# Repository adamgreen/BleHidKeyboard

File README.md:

# BLE HID Keyboard
A project to convert a [Perixx PERIDUO-307B USB wired keyboard](https://www.amazon.com/Perixx-PERIBOARD-407B-Mini-Keyboard-Dimension/dp/B0053O9ZNQ/) to wireless Bluetooth Low Energy (BLE). The conversion is accomplished by replacing the original PCB with the one documented here which uses a [Nordic nRF51422](https://www.nordicsemi.com/eng/Products/ANT/nRF51422) BLE capable ARM Cortex-M0 microcontroller. This repository includes the Eagle CAD PCB design files and firmware source code.

## Bill of Materials
Description | Quantity | Part Number(s)
------------|----------|---------------
[Perixx PERIDUO-307B USB wired keyboard](https://www.amazon.com/Perixx-PERIBOARD-407B-Mini-Keyboard-Dimension/dp/B0053O9ZNQ/) | 1 |
[SODIAL 3W LED Mini Pen Torch Flashlight 2xAAA](https://www.amazon.com/gp/product/B01J58ZHOG) | 1 |
[1.2kΩ Resistor - 0805](https://www.adafruit.com/product/441) | 3 | R1, R2, R3
[Microchip MCP23018 I2C I/O Expander](https://www.digikey.com/product-detail/en/microchip-technology/MCP23018-E-SS/MCP23018-E-SS-ND/1999506) | 2 | IC1, IC2
[Samtec 2x5 SMT Micro Header](https://www.digikey.com/product-detail/en/FTSH-105-01-L-DV-K/SAM8799-ND/1875039) | 1 | JP1
[Dynastream N5150M5CD - nRF51422 Module](https://www.digikey.com/products/en?keywords=N5150M5CD) | 1 | U1
[Green SMT LED](https://www.digikey.com/product-detail/en/kingbright/APTD3216LCGCK/754-2049-1-ND/7043101) | 3 | LED_CAPS, LED_CONNECT, LED_NUM LED

It also requires a 2x13 ribbon cable connector harvested from the original PCB using a [Chip Quick SMD Removal Kit](https://www.adafruit.com/product/2660).

## Firmware Build
I have only tested the build on macOS but it will probably work on other Posix operating systems too.

**Note:** Building the firmware and deploying it to the nRF51 requires the **mergehex** and **nrfjprog** tools. The archive for your OS can be downloaded from the _Downloads_ tab of the [nRF51422 product page](https://www.nordicsemi.com/eng/Products/Bluetooth-low-energy/nRF51422). You will also need a SEGGER J-Link JTAG/SWD Debugger. If your projects are of a non-commercial nature, you can use this [low cost module available from Adafruit](https://www.adafruit.com/product/3571).

* ```make sdk``` will download and install the required Nordic SDK. This should only need to be done once.
* ```make flash_softdevice``` will install the required Nordic SoftDevice on the nRF51422 microcontroller using the J-Link debugger. This will typically only need to be done once for each microcontroller.
* ```make all``` will build the keyboard firmware.
* ```make flash```will build the keyboard firmware and deploy it using the J-Link debugger.
* ```make generate_patches``` can be used to generate diffs for any files that you have modified in the [config/ subfolder](https://github.com/adamgreen/BleHidKeyboard/tree/master/firmware/config) so that you can commit and share them via git.

## Photos
**Perixx PERIDUO-307B USB Wired Keyboard**<br>
<br>

**Inside of Keyboard with Original PCB**<br>
<br>

**Inside of Keyboard with New BLE PCB**<br>
<br>

**Peeking Under Membrane at New BLE PCB**<br>
<br>

**Inside of Keyboard After Modifications**<br>
<br>

**Keyboard with 2xAAA Torchlight as Battery Pack**<br>
<br>

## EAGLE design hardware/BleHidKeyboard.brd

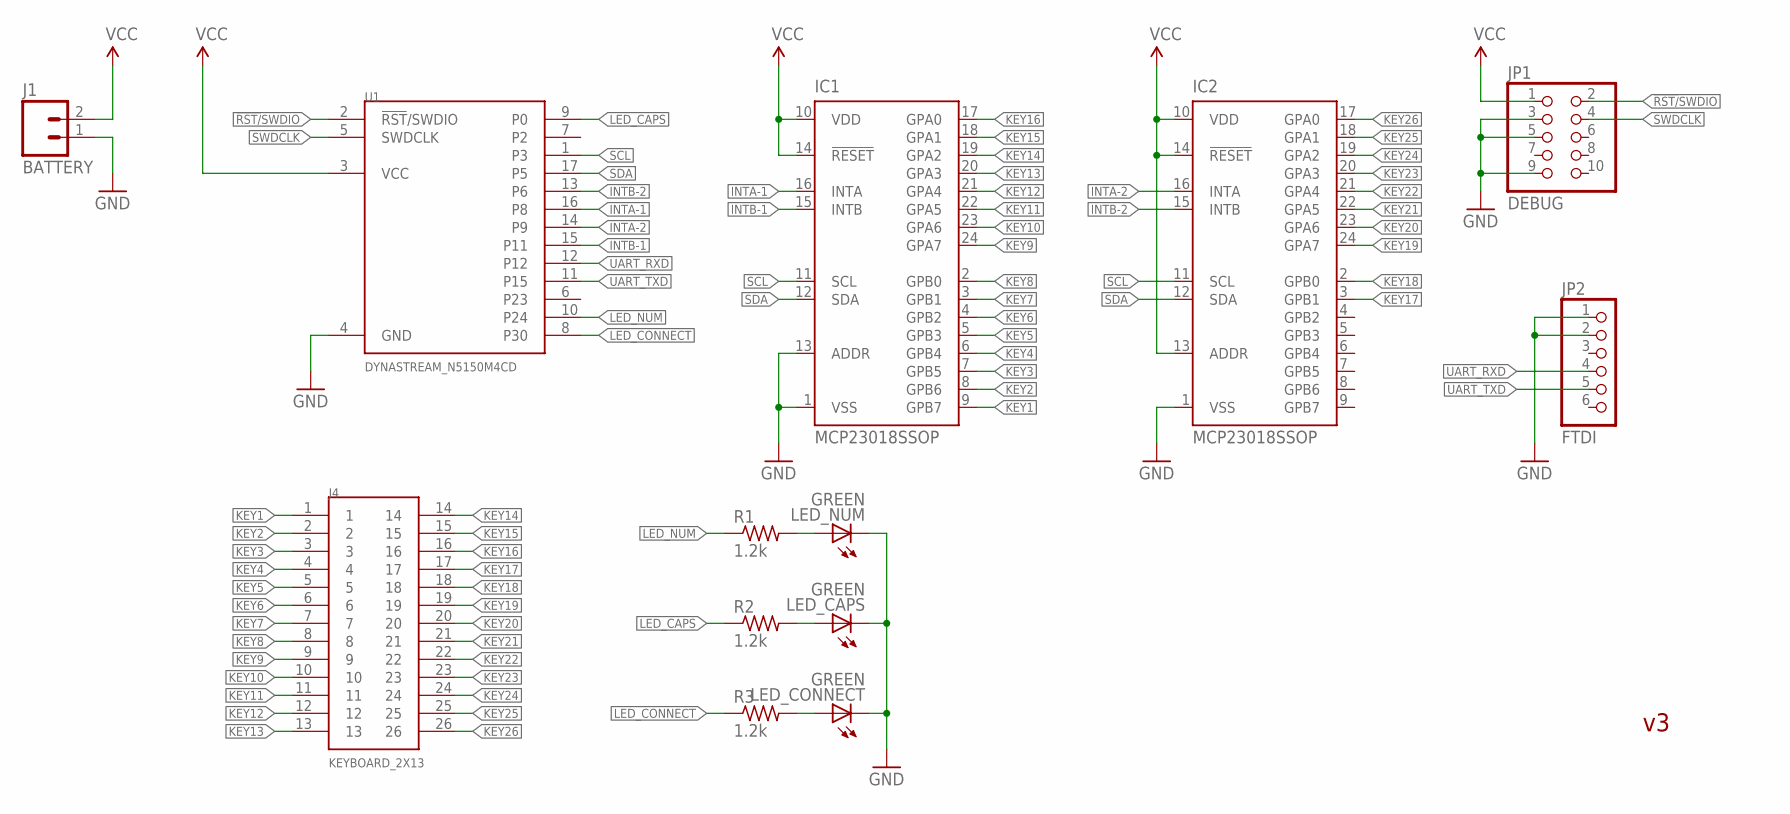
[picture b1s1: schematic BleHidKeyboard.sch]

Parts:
IC1, IC2: MCP23018SSOP; SSOP24
J1: BATTERY; 1X02_NO_SILK
J4: KEYBOARD_2X13
JP1: DEBUG; FTSH-105
JP2: FTDI; 1X06-CLEAN
LED_CAPS: GREEN; CHIPLED_1206
LED_CONNECT: GREEN; CHIPLED_1206
LED_NUM: GREEN; CHIPLED_1206
R1, R2, R3: 1.2k; R0805
U1: DYNASTREAM_N5150M4CD; N5150M4CD

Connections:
!RST/!SWDIO: JP1.2, U1.2 (!RST!/SWDIO)
GND: IC1.1 (VSS), IC1.13 (ADDR), IC2.1 (VSS), J1.1, JP1.3, JP1.5, JP1.9, JP2.1, JP2.2, LED_CAPS.C, LED_CONNECT.C, LED_NUM.C, U1.4 (GND)
INTA-1: IC1.16 (INTA), U1.16 (P8)
INTA-2: IC2.16 (INTA), U1.14 (P9)
INTB-1: IC1.15 (INTB), U1.15 (P11)
INTB-2: IC2.15 (INTB), U1.13 (P6)
KEY1: IC1.9 (GPB7), J4.1
KEY2: IC1.8 (GPB6), J4.2
KEY3: IC1.7 (GPB5), J4.3
KEY4: IC1.6 (GPB4), J4.4
KEY5: IC1.5 (GPB3), J4.5
KEY6: IC1.4 (GPB2), J4.6
KEY7: IC1.3 (GPB1), J4.7
KEY8: IC1.2 (GPB0), J4.8
KEY9: IC1.24 (GPA7), J4.9
KEY10: IC1.23 (GPA6), J4.10
KEY11: IC1.22 (GPA5), J4.11
KEY12: IC1.21 (GPA4), J4.12
KEY13: IC1.20 (GPA3), J4.13
KEY14: IC1.19 (GPA2), J4.14
KEY15: IC1.18 (GPA1), J4.15
KEY16: IC1.17 (GPA0), J4.16
KEY17: IC2.3 (GPB1), J4.17
KEY18: IC2.2 (GPB0), J4.18
KEY19: IC2.24 (GPA7), J4.19
KEY20: IC2.23 (GPA6), J4.20
KEY21: IC2.22 (GPA5), J4.21
KEY22: IC2.21 (GPA4), J4.22
KEY23: IC2.20 (GPA3), J4.23
KEY24: IC2.19 (GPA2), J4.24
KEY25: IC2.18 (GPA1), J4.25
KEY26: IC2.17 (GPA0), J4.26
LED_CAPS: R2.1, U1.9 (P0)
LED_CONNECT: R3.1, U1.8 (P30)
LED_NUM: R1.1, U1.10 (P24)
unnamed: LED_NUM.A, R1.2
unnamed: LED_CAPS.A, R2.2
unnamed: LED_CONNECT.A, R3.2
SCL: IC1.11 (SCL), IC2.11 (SCL), U1.1 (P3)
SDA: IC1.12 (SDA), IC2.12 (SDA), U1.17 (P5)
SWDCLK: JP1.4, U1.5 (SWDCLK)
UART_RXD: JP2.4, U1.12
UART_TXD: JP2.5, U1.11 (P15)
VCC: IC1.10 (VDD), IC1.14 (!RESET), IC2.10 (VDD), IC2.13 (ADDR), IC2.14 (!RESET), J1.2, JP1.1, U1.3 (VCC)

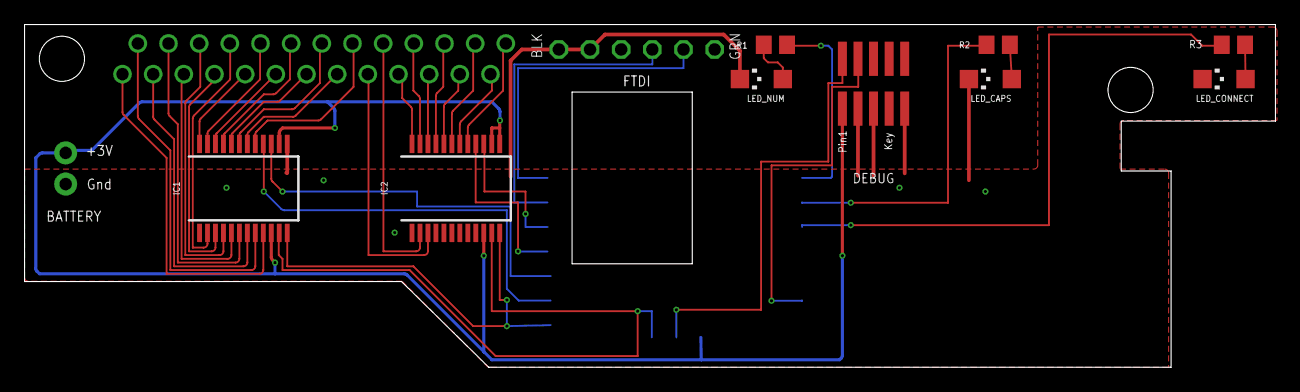
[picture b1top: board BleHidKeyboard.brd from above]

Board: 2 copper layers, 102.0 x 27.9 mm, 13 parts (0 on the bottom side), 44 nets.

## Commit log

2017-11-24 Initial commit
    I am starting from some code that I wrote previously which interfaces
    to an old AT style keyboard and exposes it as a BLE HID wireless
    keyboard.
    Future commits will change it to interface directly to the keyboard
    matrix in a modern keyboard, replacing the existing USB electronics.
2017-11-27 Initial MCP23018 I/O expander driver
    I also hacked some code into main.c to verify basic functionality of
    the I/O expander when connected to a single column of 2 row of
    switches.
2017-11-27 Cleanup MCP23018.c module
    Just removing old code that I used as a template for implementing this
    module. This code was already commented out. Now I am just deleting it.
2017-11-28 Handle NULL pointers in mcp23018AsyncGetGpio()
    Previously the pPortA and pPortB parameters had to be non-NULL or a
    crash would occur in the gpioReadCompletedCallback() when it attempted
    to write the resulting read data.
2017-11-28 Created KeyboardMatrix module
    Moved the existing experimental keyboard scanning code over into the
    new KeyboardMatrix module. Future work will be done to actually fill
    in a USB HID report structure based on scan results.
2017-11-29 Enable nRF ASSERTs in Makefile
    Defined DEBUG_NRF_USER to get the ASSERT macro defined by nrf_assert.h
    enabled...at least for my initial testing.
2017-11-29 Now sends 'a' and ' ' over BLE
    Pressing the button on the first row will now send an 'a' key press to
    my iOS device via BLE. Pressing the button on the second row sends a
    space.
2017-11-29 Remove AT keyboard code
    This commit removes the AT keyboard intefacing code that I used for
    the original prototype now that I have the basics of the keyboard
    matrix version built. I previously kept it around to quickly lookup
    how I did things for that version.
2018-01-03 Switch keyboard scanning timer to single shot
    Previously the timer used for scanning the keyboard matrix was setup to
    be repeating but this caused problems when the main loop was executing
    long running tasks when too many of these timer events would fill up
    the application scheduling queue. The timer is now single shot and is
    restarted each time the main loop finally gets around to running the
    callback for the previous timer tick. This will add more jitter to the
2018-01-08 Add wakeup on spacebar press
    Added kbmatrixConfigureForWakeupOnSpacebar() function which configures
    the row and column pins corresponding to the space key. The column to
    which the space key is connected is pulled low and the row to which it
    is attached is setup to pull the interrupt pin on the MCP23018 low
    when the space key closes the circuit. The MCP23018 interrupt pin is
    configured as a wakeup source for the nRF51 CPU.
2018-03-03 Initial commit of schematic
2018-03-03 Adding documents
    These are documents related to the hardware devices used in the
    keyboard circuit.
2018-03-03 Update schematic to pass ERC
2018-03-15 Version 1 of PCB layout
    This is the version that I sent to OSHPark to have manufactured on
    3/14/2018.
2018-05-01 Firmware sending first key presses from real key presses
    I now have PCBs soldered up with the keyboard mylar connected. This
    firmware is able to process presses on this keyboard and send them
    to my iPhone via BLE. It is missing some stuff like caps/numlock LED,
    sleep support, etc that will be added in future commits.
    This commit includes:
    * keycodes/main.c which I build with a simple "gcc main.c". When run it
2018-05-01 Change IO direction and pull GPIO pin low in one async op
    Previously the IO direction was changed synchronously from within the
    timer intterupt and then the GPIO async write was started. Now they
    are both done asynchronously through a new function added to the
    MPC23018 module.
    I now malloc the I2C transaction queue dynamically since the required
    size really depends on how many MCP23018 objects you have and how you
2018-05-01 Added Caps & Num Lock support
    Now processes the HID output reports to determine the PC's num & caps
    lock state and use them to update the corresponding LEDs on my PCB.
2018-05-01 Put nRF51 to sleep if FN + F1 (Sleep) key is pressed
    Make sure to turn caps & num lock LED off before putting device to
    sleep.
2018-05-01 Keyboard now wakes up on spacebar press
    Added code which figures out the column and row for the space bar in
    the current key mapping. Uses this information to pull that column low
    and configure that row pin to generate an interrupt if pulled low
    before entering sleep.
2018-05-01 Erase BLE bonding information if Delete pressed on startup
    kbmatrixInit() now checks to see if the Delete key is pressed during
    initialization. This can be used to erase the BLE pairing bonds.
    I pulled the timer startup code out of the init path and put it in
    kbmatrixStart() since starting the timers before BLE caused errors.
2018-05-02 Was always detecting Delete pressed on startup
    I was waiting for the wrong async operation to complete in
    scanKeyboardForDeleteKey(). I should have been waiting for the get to
    finish but I was waiting on the set instead.
    I also made a similar change in scanKeyboardMatrixCallback().
2018-05-02 Don't need to connect as often as we were
    My maximum typing rate target is about 16Hz so I used that as a guide
    to how long the minimum and maximum connection interval should be.
    This helps reduce the average current usage by ~100uA.
2018-05-02 Switch to 1.2k LED current limiting resistors
    This reduces current usage by half but still leaves them bright enough
    to see.
2018-05-02 Send back actual battery level
    Now uses the ADC to sample the voltage of the battery instead of using
    a simulator to fake values to send back via the BLE battery service.
    It is quite cool that the ADC in the nRF51 can do this without using
    any external pins/connections. Internally it is able to compare 1/3Vcc
    to a 1.2VBG.
    Other updates include:
2018-05-05 Initial README
2018-05-07 Version 3 of the PCB design
    This is the design being sent off to OSHPark on May 6th, 2018.
    This version of the PCB no longer uses the 20-pin Molex connector on
    the bottom of the Dynastream N5150M5CD module and instead uses the
    pads around the perimeter of the N5150M4CD module (actually the same
    module but without the Molex and SWD connectors) instead. The module
    will now mount on the bottom of the PCB with the module can sticking up
2018-05-07 Add schematic/PCB images
2018-05-07 Add PCB and schematic to README
2018-05-07 Fix some text alignment issues in schematic
    I changed the UI options to only use vectored fonts and that broke a
    few things in the schematic.
2018-05-07 Add photos of keyboard w/ original PCB
2018-05-07 Add keyboard photos to README
2018-05-07 Add photo w/ version 1 PCB in keyboard
    This version of the PCB doesn't work in the keyboard since the module
    sticks up too high and interferes with keyboard membrane. Version 3
    fixes that problem.
2018-05-07 Add version 1 photo to README
2018-06-03 Switch from QWERTY to ABC keyboard layout
    Can set KEYBOARD_ABC to 0 in KeyMappings.h to switch back to QWERTY
    layout.
2018-06-07 Enable MITM 6-digit passkey pairing
    Changes include:
    * Many of the GATT attributes are now marked to use encryption with
    MITM (Man In The Middle) protection enabled.
    * MITM protection is enabled when enabling the device manager. The
    BLE_GAP_IO_CAPS_KEYBOARD_ONLY bit is set to indicate that this device
    only has a keyboard and no display. This forces the central device to
2019-02-22 Add photos of completed keyboard
2019-02-22 Fix photo filenames.
    I used the wrong year as the filenames.
2019-02-22 Update README
    Show photos of final build.
2019-02-23 Add labels for back of keyboard
    I created two labels that I could print out and place on the back of
    the keyboard.
    * A diagram showing how the batteries are to be inserted.
    * Notes about special keypresses and meaning of Scroll Lock LED.

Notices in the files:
parts and their libraries:
SparkFun-Connectors: Licensing: Creative Commons ShareAlike 4.0 International - https://creativecommons.org/licenses/by-sa/4.0
adam_custom: Released under the Creative Commons
adam_custom: https://creativecommons.org/licenses/by-sa/4.0
